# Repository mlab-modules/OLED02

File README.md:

# OLED02 Display with I2C interface

The **OLED02A** is a simplified variant of the MLAB [OLED01](https://github.com/mlab-modules/OLED01) module. It features a 1.3-inch blue OLED display using the SSD1306BZ controller and communicates over an I²C interface.

## Features
- **Display**: 1.3-inch passive matrix OLED with a resolution of 128x64 pixels.
- **Color**: Blue.
- **Controller**: SSD1306BZ.
- **Interface**: I²C.
- **Power Supply**:
  - Logic: 3.0 V typical (2.8 V min, 3.3 V max).
  - Display: Internally generated by integrated DC/DC converter.
- **Address Configuration**: Default I²C address is `0x3C`, changeable to `0x3D` via onboard jumper.
- **Mounting**:
  - Horizontal MLAB standard.
  - Optional vertical placement using a 3D-printed holder.

## Electrical Characteristics

- **Operating Voltage (Logic)**: 2.8 V to 3.3 V
- **Operating Current**: \~10 mA @ 12 V VCC (internally generated)
- **Interface Voltage Levels**: TTL-compatible (0 to 3.3 V)

## Optical Characteristics

- **Contrast Ratio**: 2000:1
- **Brightness**: 60–80 cd/m² (typical with 50% checkboard)
- **Viewing Angle**: 160° (H and V)
- **Response Time**: 10 µs (rise and fall)
- **Display Technology**: Passive matrix
- **Pixel Size**: 0.148 mm x 0.148 mm
- **Dot Pitch**: 0.17 mm x 0.17 mm
- **Active Area**: 21.738 mm x 10.858 mm

## Mechanical Parameters

- **Board Dimensions**: 40.14 mm x 40.14 mm
- **Board Thickness**: 1.6 mm
- **Mounting**: Compatible with standard MLAB module placement

## I²C Pin Configuration (Standard MLAB I2C Layout)

| Pin | Name | Description       |
| --- | ---- | ----------------- |
| 1   | GND  | Ground            |
| 2   | SDA  | Serial Data       |
| 3   | 3V3  | 3.3V power supply |
| 4   | SCL  | Serial Clock      |
| 5   | GND  | Ground            |

## I²C Address Selection

The OLED02A module uses `0x3C` as its default I²C address. By bridging the onboard address jumper, the address switches to `0x3D`.

## Notes

- OLED02A omits certain advanced features present in OLED01 to simplify integration and reduce cost.
- The module uses only the I²C interface; SPI and parallel interfaces supported by the SSD1306BZ are not routed.
- Ensure proper handling precautions for OLEDs to prevent damage or screen burn-in.
- Refer to the [SSD1306 datasheet](https://www.vishay.com/doc?37902) for command interface details.

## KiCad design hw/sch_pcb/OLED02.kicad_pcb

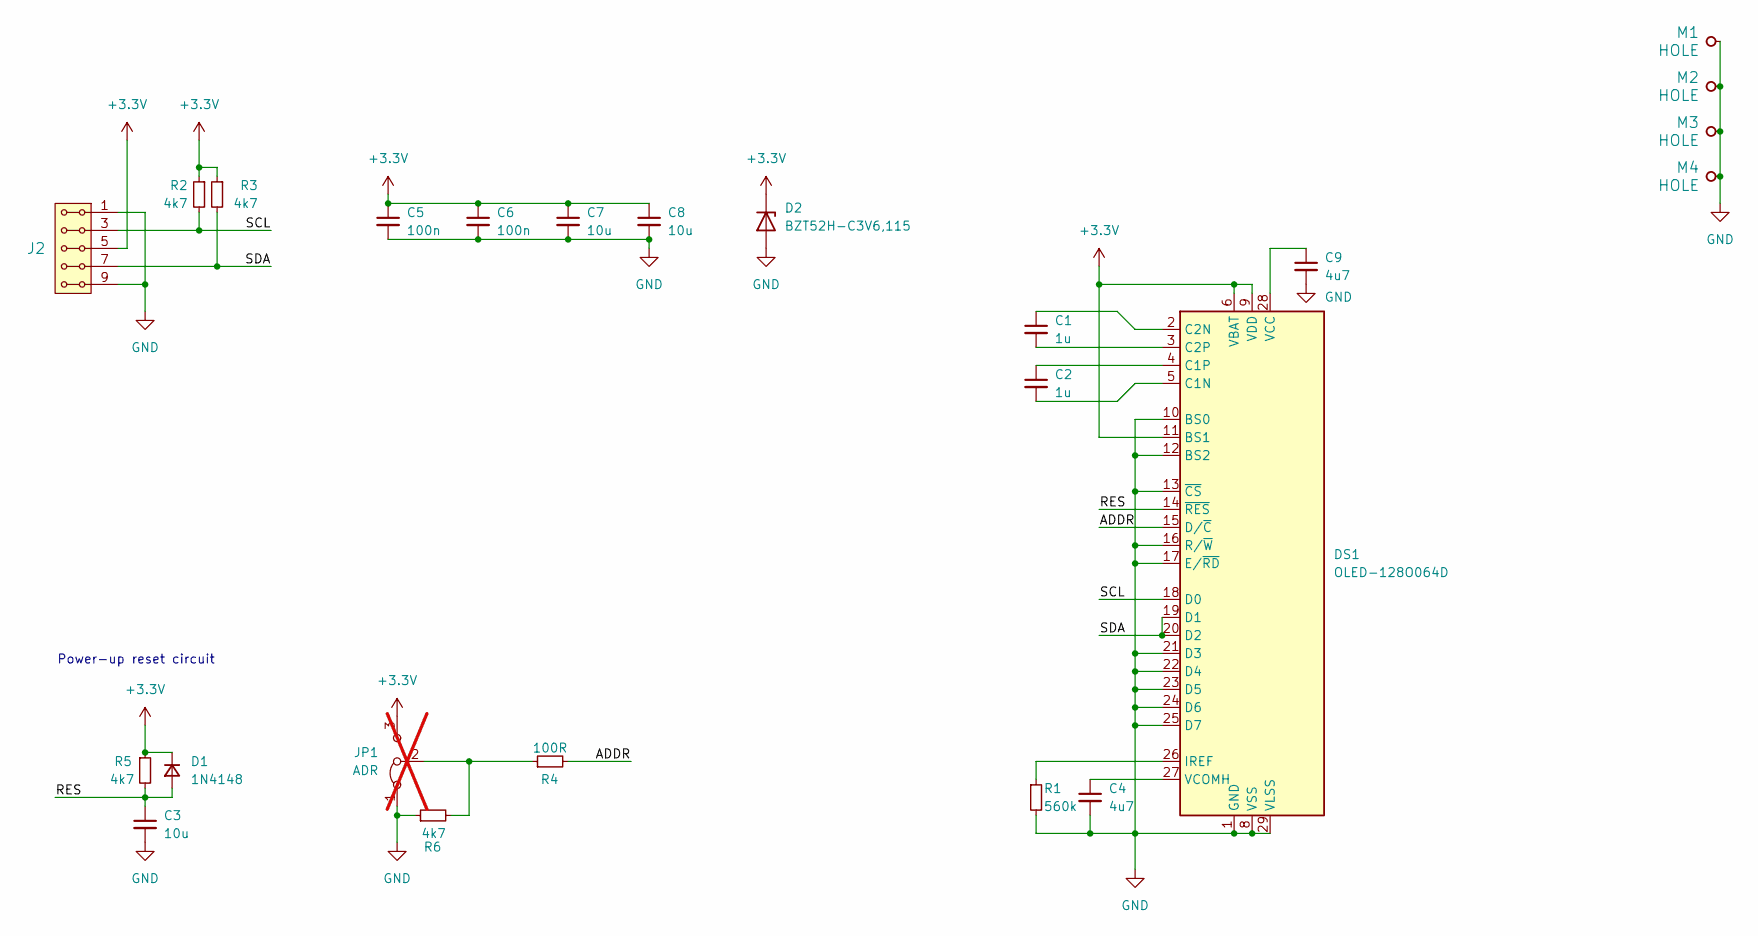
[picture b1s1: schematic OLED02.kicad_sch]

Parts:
C1, C2: 1u; C_0805_2012Metric
C3, C7, C8: 10u; C_0805_2012Metric
C4, C9: 4u7; C_0805_2012Metric
C5, C6: 100n; C_0805_2012Metric
D1: 1N4148; D_0805_2012Metric
D2: BZT52H-C3V6,115; D_SOD-123F
DS1: OLED-128O064D
J2: HEADER_2x05_PARALLEL; PinHeader_2x05_P2.54mm_Vertical
JP1: ADR; PinHeader_1x03_P2.54mm_Vertical; not fitted
M1, M2, M3, M4: HOLE; MountingHole_3mm
R1: 560k; R_0805_2012Metric
R2, R3, R5, R6: 4k7; R_0805_2012Metric
R4: 100R; R_0805_2012Metric

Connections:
+3.3V: C5.1, C6.1, C7.1, C8.1, D1.1 (K), D2.1 (K), DS1.6 (VBAT), DS1.9 (VDD), DS1.11 (BS1), J2.5, J2.6, JP1.3 (B), R2.1, R3.1, R5.1
/ADDR: DS1.15 (D/~C), R4.2
/RES: C3.1, D1.2 (A), DS1.14 (~RES), R5.2
/SCL: DS1.18 (D0), J2.3, J2.4, R2.2
/SDA: DS1.19 (D1), DS1.20 (D2), J2.7, J2.8, R3.2
GND: C3.2, C4.2, C5.2, C6.2, C7.2, C8.2, C9.2, D2.2 (A), DS1.1 (GND), DS1.8 (VSS), DS1.10 (BS0), DS1.12 (BS2), DS1.13 (~CS), DS1.16 (R/~W), DS1.17 (E/~RD), DS1.21 (D3), DS1.22 (D4), DS1.23 (D5), DS1.24 (D6), DS1.25 (D7), DS1.29 (VLSS), DS1.30 (GND), J2.1, J2.2, J2.9, J2.10, JP1.1 (A), M1.1, M2.1, M3.1, M4.1, R1.2, R6.1
unnamed: C2.2, DS1.5 (C1N)
unnamed: C2.1, DS1.4 (C1P)
unnamed: C1.1, DS1.2 (C2N)
unnamed: C1.2, DS1.3 (C2P)
unnamed: DS1.26 (IREF), R1.1
unnamed: C9.1, DS1.28 (VCC)
unnamed: C4.1, DS1.27 (VCOMH)
unnamed: JP1.2 (C), R4.1, R6.2

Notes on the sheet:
Power-up reset circuit

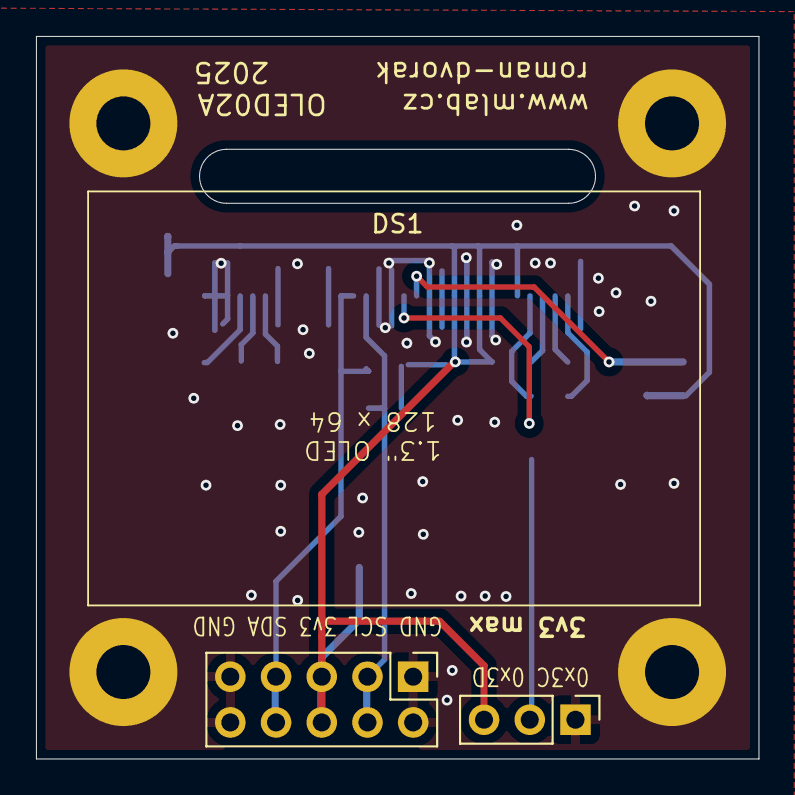
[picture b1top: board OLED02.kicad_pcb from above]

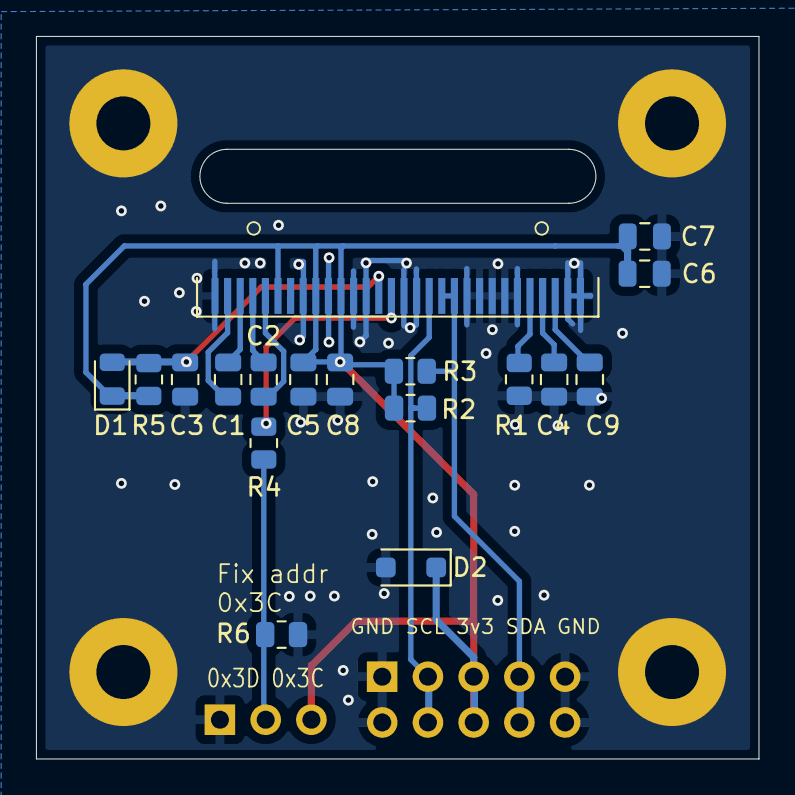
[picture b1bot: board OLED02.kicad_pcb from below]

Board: 2 copper layers, 40.1 x 40.1 mm, 24 parts (18 on the bottom side), 14 nets.

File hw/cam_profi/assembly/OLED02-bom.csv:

Component,Description,Part,References,Value,Footprint,Quantity Per PCB,Datasheet,sim.device,sim.pins,ust_id
1,"Unpolarized capacitor, small symbol",C_Small,C5C6,100n,C_0805_2012Metric,2,~,,,
2,"Unpolarized capacitor, small symbol",C_Small,C1C2,1u,C_0805_2012Metric,2,~,,,
3,"Unpolarized capacitor, small symbol",C_Small,C4,4u7,C_0805_2012Metric,1,~,,,
4,"Unpolarized capacitor, small symbol",C_Small,C3C7C8,10u,C_0805_2012Metric,3,~,,,
5,"Diode, small symbol",D_Small,D1,1N4148,D_0805_2012Metric,1,~,D,1=K 2=A,
6,Zener diode,D_Zener,D2,"BZT52H-C3V6,115",D_SOD-123F,1,~,,,650b35ab462c6d9e720543d0
7,OLED display 128x64,OLED-128O064D,DS1,OLED-128O064D,OLED-128O064D,1,https://www.vishay.com/docs/37902/oled128o064dbpp3n00000.pdf,,,
8,"2x05 2.54 mm pitch header, 2 pins next to each other are connected",HEADER_2x05_PARALLEL,J2,HEADER_2x05_PARALLEL,PinHeader_2x05_P2.54mm_Vertical,1,,,,
9,"Resistor, small symbol",R_Small,R4,100R,R_0805_2012Metric,1,~,,,
10,"Resistor, small symbol",R_Small,R2R3R5R6,4k7,R_0805_2012Metric,4,~,,,
11,"Resistor, small symbol",R_Small,R1,560k,R_0805_2012Metric,1,~,,,

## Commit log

2025-02-22 initial version
2025-02-22 add assets
2025-02-22 Update workflow files
2025-02-22 Update metadata files
2025-02-22 rename folder
2025-02-22 Update actions products
2025-02-25 Update status and fab Layer.
2025-03-13 update kicad version
2025-03-13 update assets
2025-03-13 testing fw
2025-04-12 Update documentation.
2025-04-12 Improve documentation by adding new photos.
2025-04-12 Update README.md
    Fix link to images.
2025-04-12 Update metadata.yaml
    Module reaches the production phase.
